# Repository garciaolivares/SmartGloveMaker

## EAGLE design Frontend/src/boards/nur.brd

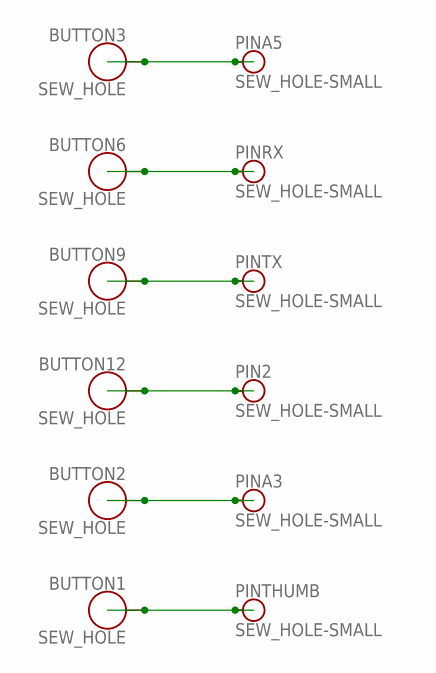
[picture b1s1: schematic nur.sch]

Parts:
BUTTON1, BUTTON2, BUTTON3, BUTTON6, BUTTON9, BUTTON12: SEW_HOLE; SIMPLE_HOLE
PIN2: SEW_HOLE-SMALL; SIMPLE_HOLE_SM
PINA3, PINA5: SEW_HOLE-SMALL; SIMPLE_HOLE_SM
PINRX: SEW_HOLE-SMALL; SIMPLE_HOLE_SM
PINTHUMB: SEW_HOLE-SMALL; SIMPLE_HOLE_SM
PINTX: SEW_HOLE-SMALL; SIMPLE_HOLE_SM

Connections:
unnamed: BUTTON1.P$1, PINTHUMB.P$1
unnamed: BUTTON2.P$1, PINA3.P$1
unnamed: BUTTON12.P$1, PIN2.P$1
unnamed: BUTTON9.P$1, PINTX.P$1
unnamed: BUTTON6.P$1, PINRX.P$1
unnamed: BUTTON3.P$1, PINA5.P$1

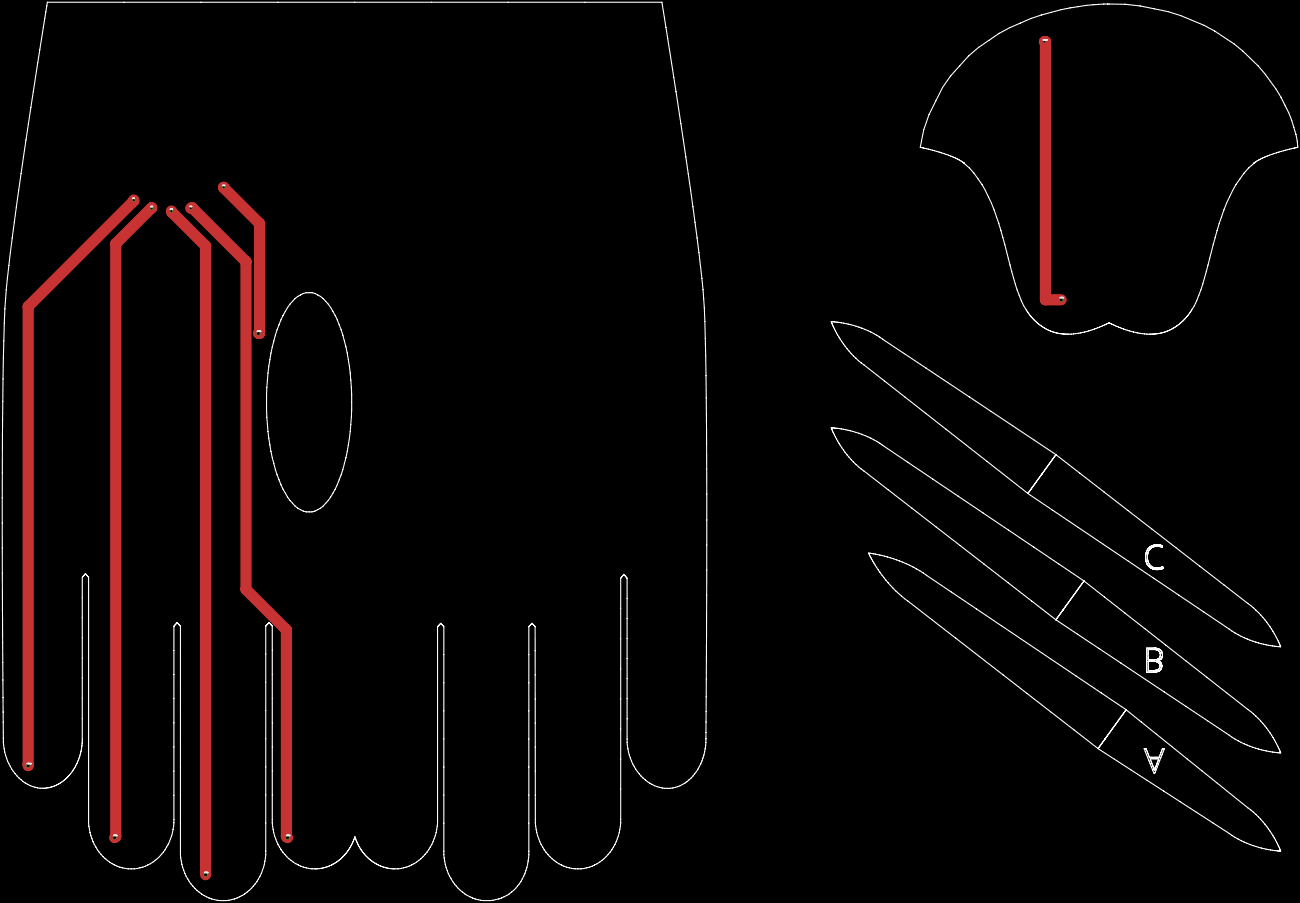
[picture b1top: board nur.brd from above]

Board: 2 copper layers, 627.5 x 800.1 mm, 12 parts (0 on the bottom side), 6 nets.

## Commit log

2018-11-27 Last Version Back and Front
2018-11-27 Adding Backend
2018-12-03 Dynamic mapping between buttons and pins
2019-01-08 Documentation

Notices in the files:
parts and their libraries:
SparkFun-Retired: Licensing: Creative Commons ShareAlike 4.0 International - https://creativecommons.org/licenses/by-sa/4.0
